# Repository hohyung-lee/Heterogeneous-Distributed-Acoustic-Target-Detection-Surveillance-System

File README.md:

# [지능형 국지 방어] 이기종 분산 처리 기반 음향 표적 탐지 및 지향성 감시 체계

**Heterogeneous Distributed Acoustic Target Detection & Surveillance System**

---

## 1. 프로젝트 목적 및 배경 (Background & Objectives)

### 방산 분야 적용

현대 전장 및 주요 보안 시설의 대드론(Anti-Drone) 체계 및 저격수 탐지 시스템에 적용되는 **'음향-시각 융합 복합 센서 체계'** 프로토타입 개발

### 이기종 분산 아키텍처 채택

단일 보드에서 모든 연산을 처리할 경우 발생하는 모터의 역기전력(Back-EMF) 및 고성능 프로세서의 스위칭 노이즈(Ground Bounce)가 초정밀 아날로그 오디오 신호에 치명적인 간섭(EMI)을 일으킴. 이를 원천 차단하기 위해 **고속 음향 처리 전용 FPGA 하드웨어**와 **영상/모터 제어용 GPU 비전 노드(Jetson)**를 물리적으로 분리하는 체계 연동 설계를 적용함.

---

## 2. 시스템 아키텍처 및 체계 연동 조감도 (System Architecture)

### Node 1 — Sensor Node (Custom FPGA Board)

```
Sound Target
  ↓ (Acoustic Wave)
4x Analog MEMS Mic
  ↓
Differential Driver (THS4551)
  ↓
ADS1274 (24-bit ADC, Simultaneous Sampling)
  ↓
Xilinx Artix-7 FPGA
  (Data Capture / Channel Sync / TDOA-DOA / UDP Packetization)
  ↓
Ethernet PHY (LAN8720A) → HR911105A (MagJack)
  ↓
UDP Transmission : "Target at θ°"
```

### 연결 인터페이스

**Standard Ethernet Cable**

### Node 2 — Command & Vision Node (Jetson Orin Nano)

```
Jetson Orin Nano
  (Direction Data Receive + Vision Processing + AI)
  ├── (PWM / GPIO) → 2-Axis Pan-Tilt Motor (Rotate to Target Direction)
  └── (MIPI / USB) → Camera Module (Target Tracking & Imaging)
```

### 보드 구성 상세

| 구분                              | 명칭                                   | 설명                                                                                                                    |
| --------------------------------- | -------------------------------------- | ----------------------------------------------------------------------------------------------------------------------- |
| **Sensor Deck**             | 마이크로폰 도터보드 (Protruding Array) | 4채널 아날로그 MEMS 마이크와 디커플링 커패시터만 실장, 3D 프린팅 하우징 외부 최상단으로 돌출 배치                       |
| **Processing & Power Core** | 메인보드 (Enclosed Base)               | Artix-7 FPGA, 차동 드라이버(FDA), ADC, 전원부, Ethernet PHY, MagJack 등 노이즈/발열 발생원을 3D 하우징 내부에 밀폐 실장 |
| **Interface**               | Board-to-Board 연결                    | 저레벨 아날로그 마이크 출력 및 전원 라인의 무결성 유지를 위해 쉴딩 처리된 FPC 케이블 체결                               |

---

## 3. 하드웨어 주요 사양 (Hardware Specifications — Sensor Node)

| 항목                        | 사양                                                                                                   |
| --------------------------- | ------------------------------------------------------------------------------------------------------ |
| **Main Processor**    | AMD Xilinx Artix-7 (XC7A35T-1CSG325C) — Bare-metal Chip-down                                          |
| **Sensor Array**      | Infineon IM68A130A Analog MEMS Microphone × 4ea                                                       |
| **Analog Front-End**  | TI THS4551 (Fully Differential Amplifier)                                                              |
| **Data Converter**    | TI ADS1274 (24-bit Simultaneous Sampling ADC)                                                          |
| **Network Interface** | Microchip LAN8720A (10/100M Ethernet PHY, RMII) + HanRun HR911105A (MagJack) + 50MHz Active Oscillator |
| **Configuration**     | Winbond W25Q32 (32Mbit SPI Flash) / JTAG Interface                                                     |
| **PCB 스펙**          | 4-Layer FR-4 (L1: Signal/USER – L2: Solid GND – L3: VCC/Power – L4: Signal/USER), 두께 1.6mm        |
| **EDA Tool**          | KiCad (회로도, PCB Artwork, 3D Rendering, Impedance Calculation)                                       |

### Power Tree

| 레일 | 용도          | 소자                          |
| ---- | ------------- | ----------------------------- |
| 1.0V | FPGA Core     | TI TLV62569 Buck Converter    |
| 3.3V | FPGA I/O      | TI TLV62569 Buck Converter    |
| 3.3V | MEMS Mic      | TI LP5907 Ultra-Low Noise LDO |
| 1.8V | ADC DVDD      | TI LP5907 1.8V LDO            |
| 2.5V | ADC Reference | TI REF5025                    |

### Form Factor

| 보드          | 크기                                               |
| ------------- | -------------------------------------------------- |
| Mainboard     | 100mm × 100mm (DFM 및 양산 단가 최적화 규격)      |
| Daughterboard | 50mm × 50mm 이내 십자형 구조 (마이크 어레이 전용) |

---

## 4. 하드웨어 설계 핵심 기술 (Core Hardware Design Technologies)

### ① 물리적 노이즈 격리 및 전원 무결성 (Power Integrity)

- **시스템 분리** — 모터 구동부와 고성능 GPU(Jetson)를 물리적으로 분리하여 아날로그 센서부의 GND 흔들림 및 전원 강하 현상 방지
- **초저노이즈 전원 트리(Power Tree)**
  - FPGA Core(1.0V) 및 I/O(3.3V) : 스위칭 강하 효율을 위한 고성능 Buck Converter 적용
  - MEMS Mic(3.3V), ADC Analog Rail, ADC DVDD(1.8V) : 디지털 스위칭 노이즈 차단을 위해 별도의 초저노이즈 LDO 및 기준 전압 레퍼런스 적용
  - Ethernet PHY 아날로그 전원은 Ferrite Bead 후단의 ETH_3V3_A로 분리 공급

### ② 고속 신호 무결성 (Signal Integrity) 및 4-Layer 임피던스 제어

- **4-Layer Stackup 최적화** — `L1(Top Signal) - L2(Solid GND) - L3(Power/VCC) - L4(Bottom Signal)`의 정석적인 4층 구조 채택. 2층(L2)에 끊어짐 없는 완벽한 GND 플레인을 깔아 기판 내 모든 고속 신호의 최단 리턴 패스(Return Path)를 보장하고 고주파 방사 노이즈(EMI)를 원천 차단함.
- **차동 배선(Differential Pair)** — Ethernet PHY ↔ MagJack 간 TX/RX 라인에 대한 100Ω 차동 임피던스 매칭을 수행하며, L2 GND 레퍼런스 플레인을 기준으로 KiCad 임피던스 계산기를 통해 산출된 배선폭/간격을 Artwork에 적용함.
- **Mixed-Signal 프런트엔드** — 4채널 아날로그 마이크 출력을 FDA로 차동 변환한 뒤 ADS1274에 입력하여 공통모드 노이즈 내성 확보
- **동시 샘플링(Simultaneous Sampling)** — ADS1274의 4채널 동시 샘플링을 이용하여 TDOA 연산에 필요한 채널 간 시간 정합성 확보
- **클록 무결성(Clock Integrity)** — ADC 전용 저지터 클록과 Ethernet용 50MHz REF_CLK를 분리하여 각 인터페이스의 지터 민감도를 관리

### ③ Chip-down 기반 FPGA 인프라 자력 설계

- 기성품 평가 보드(Eval Board) 배제, FPGA 구동을 위한 최소 시스템(Minimum System) 직접 설계
- 데이터시트 분석을 통한 Power-On Reset(POR), Configuration Flash, JTAG 디버그 회로 독자 구현
- FPGA 내부 로직 : ADS1274 디지털 데이터 수집 → 채널 정렬/버퍼링 → TDOA/DOA 연산 → Ethernet UDP 패킷화

### ④ 기구-전자 통합 설계 및 음향학적 최적화 (Acoustic-Mechanical Integration)

- **음향 그림자(Acoustic Shadowing) 및 공명 차단** — 단일 보드 설계 시 대형/고발열 소자에 의한 소리 회절과 케이스 내부 빈 공간의 헬름홀츠 공명(Helmholtz Resonance) 왜곡 방지. 마이크 어레이 보드를 케이스 외부로 돌출 분리시켜 360° 완벽한 음향 시야(Line-of-Sight) 확보
- **센서 지오메트리 설계** — 공간 앨리어싱(Spatial Aliasing, ≤21.25mm @ 8kHz) 한계와 샘플링 시간 분해능을 고려하여 TDOA 알고리즘 최적의 30~40mm 정사각형 마이크 배치 간격 도출

---

## 5. 기대 효과 및 포트폴리오 소구점 (Expected Impact)

이 프로젝트는 단위 칩 수준의 정밀한 하드웨어 설계 능력(SI/PI, 4-Layer Artwork)을 갖추었을 뿐만 아니라, 전체 무기 체계의 데이터 흐름과 노이즈 간섭(EMC)을 이해하고 최적의 아키텍처를 설계하는 **시스템 엔지니어링 역량**을 겸비했음을 증명함.

특히 방위산업에서 가장 민감하게 다루는 아날로그 센서 신호의 신뢰성, Mixed-Signal 프런트엔드 설계, FPGA 기반 실시간 TDOA/DOA 연산, 체계 연동 통신(Ethernet, UDP)을 실제 구현함으로써, 입사 후 즉각적으로 실무 하드웨어 R&D 프로젝트에 투입될 수 있는 준비된 인재임을 어필함.

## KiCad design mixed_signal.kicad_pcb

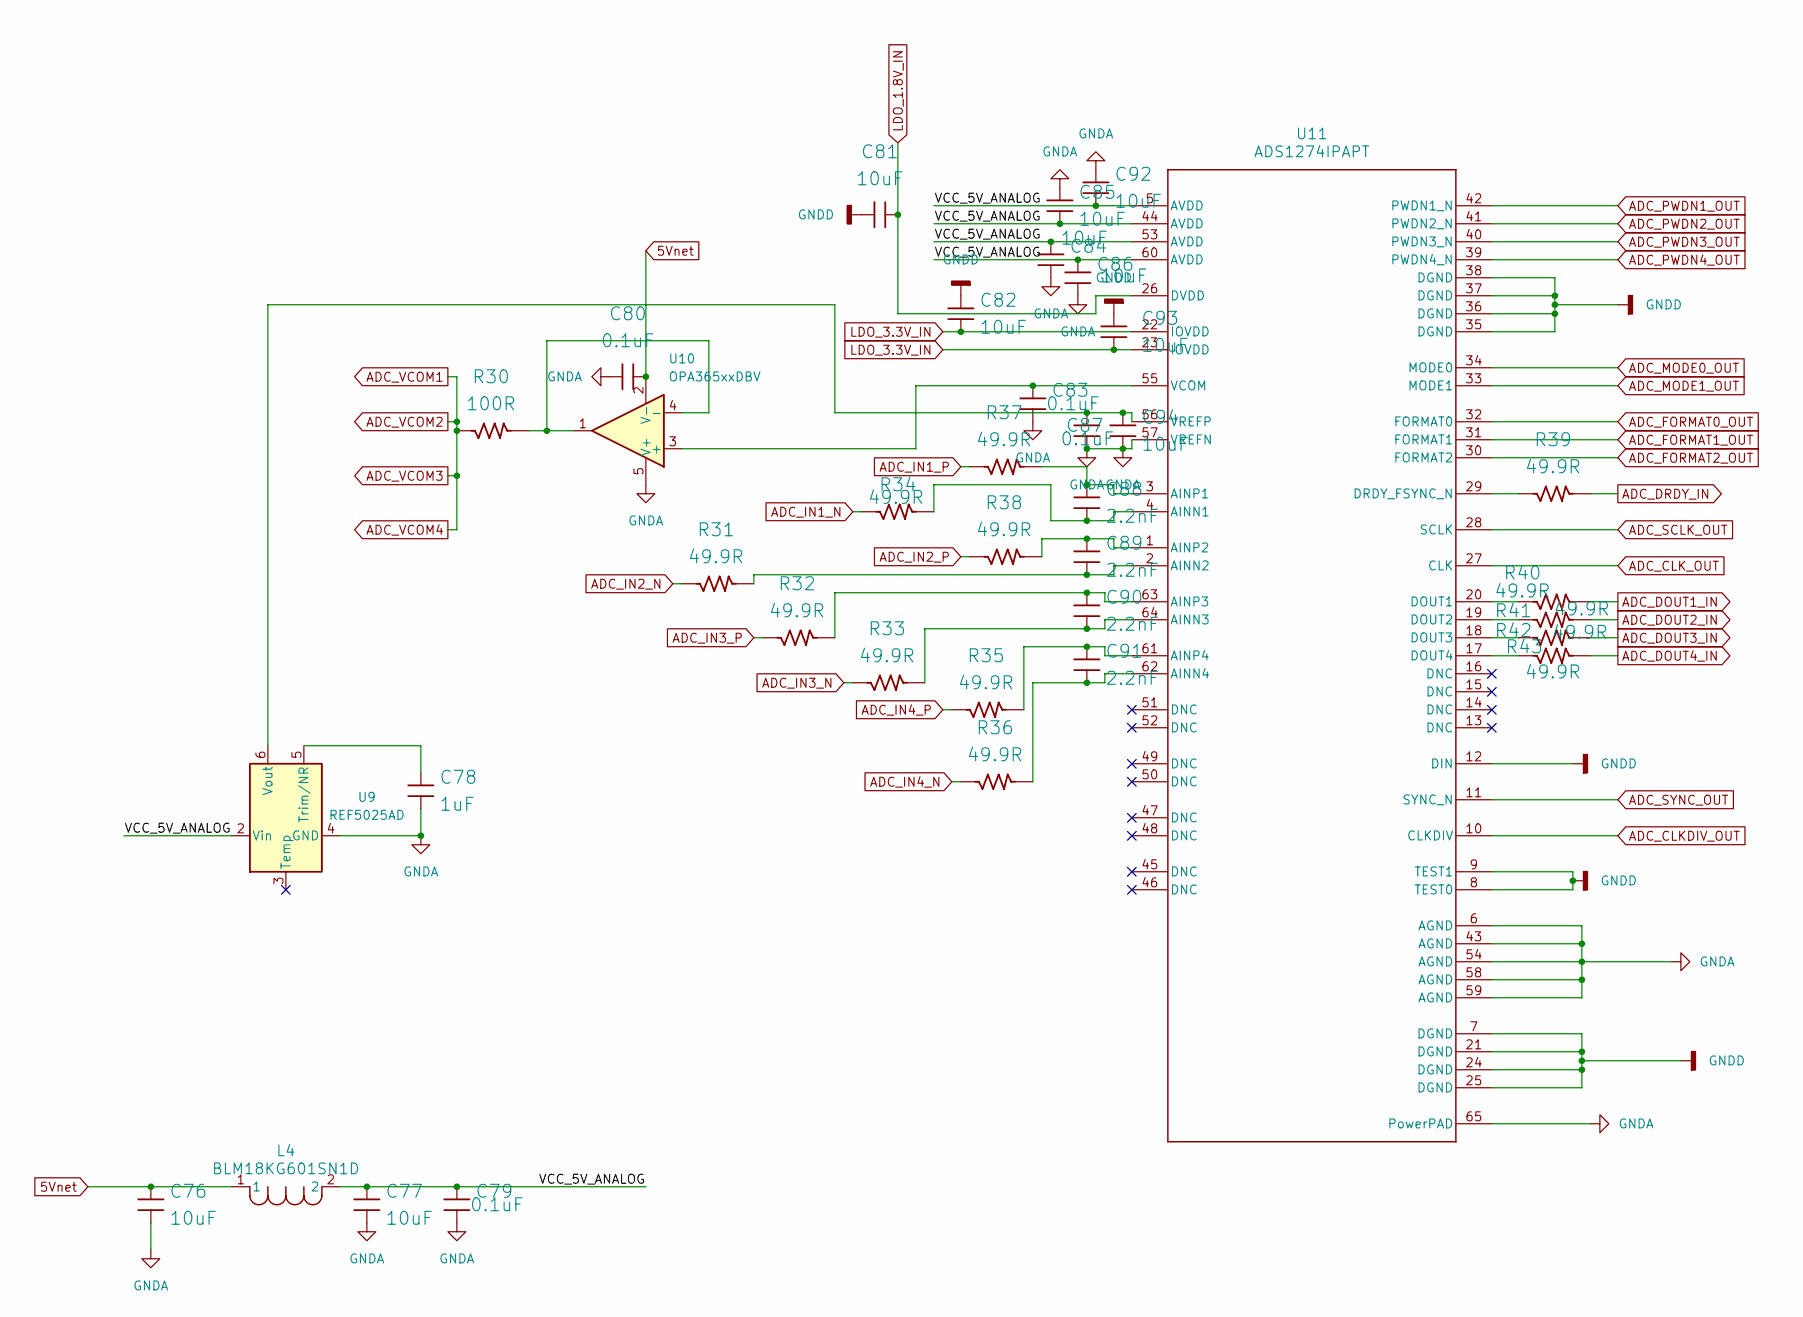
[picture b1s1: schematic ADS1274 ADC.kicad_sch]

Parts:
C76, C77, C81, C82, C84, C85, C86, C92, C93, C94: 10uF; CAP_1206; Manufacturer Part Number CL31B106KBHNNNE
C78: 1uF; CAP_0805; Manufacturer Part Number CC0805JKX7R9BB105
C79, C80, C83, C87: 0.1uF; CAP_0805; Manufacturer Part Number 08055C104JAT4A
C88, C89, C90, C91: 2.2nF; CAP_0805; Manufacturer Part Number C0805C222K5GEC7800
L4: BLM18KG601SN1D; IND_BLM18KG601SN1D_MUR
R30: 100R; RES_0805; Manufacturer Part Number WR08X1000FTL
R31, R32, R33, R34, R35, R36, R37, R38, R39, R40, R41, R42, R43: 49.9R; RES_0805; Manufacturer Part Number WR12X49R9FTL
U9: REF5025AD; SOIC-8_3.9x4.9mm_P1.27mm
U10: OPA365xxDBV; SOT-23-5
U11: ADS1274IPAPT; PAP0064G-IPC_A

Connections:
5Vnet: C76.2, C80.2, L4.1, U10.2 (V-); also elsewhere on the board
/ADS1274 ADC/VCC_5V_ANALOG: C77.2, C79.2, C84.2, C85.1, C86.2, C92.1, L4.2, U9.2 (Vin), U11.5 (AVDD), U11.44 (AVDD), U11.53 (AVDD), U11.60 (AVDD)
ADC_CLKDIV_OUT: U11.10 (CLKDIV); also elsewhere on the board
ADC_CLK_OUT: U11.27 (CLK); also elsewhere on the board
ADC_DOUT1_IN: R40.2; also elsewhere on the board
ADC_DOUT2_IN: R41.2; also elsewhere on the board
ADC_DOUT3_IN: R42.2; also elsewhere on the board
ADC_DOUT4_IN: R43.2; also elsewhere on the board
ADC_DRDY_IN: R39.2; also elsewhere on the board
ADC_FORMAT0_OUT: U11.32 (FORMAT0); also elsewhere on the board
ADC_FORMAT1_OUT: U11.31 (FORMAT1); also elsewhere on the board
ADC_FORMAT2_OUT: U11.30 (FORMAT2); also elsewhere on the board
ADC_IN1_N: R34.1; also elsewhere on the board
ADC_IN1_P: R37.1; also elsewhere on the board
ADC_IN2_N: R31.1; also elsewhere on the board
ADC_IN2_P: R38.1; also elsewhere on the board
ADC_IN3_N: R33.1; also elsewhere on the board
ADC_IN3_P: R32.1; also elsewhere on the board
ADC_IN4_N: R36.1; also elsewhere on the board
ADC_IN4_P: R35.1; also elsewhere on the board
ADC_MODE0_OUT: U11.34 (MODE0); also elsewhere on the board
ADC_MODE1_OUT: U11.33 (MODE1); also elsewhere on the board
ADC_PWDN1_OUT: U11.42 (PWDN1_N); also elsewhere on the board
ADC_PWDN2_OUT: U11.41 (PWDN2_N); also elsewhere on the board
ADC_PWDN3_OUT: U11.40 (PWDN3_N); also elsewhere on the board
ADC_PWDN4_OUT: U11.39 (PWDN4_N); also elsewhere on the board
ADC_SCLK_OUT: U11.28 (SCLK); also elsewhere on the board
ADC_SYNC_OUT: U11.11 (SYNC_N); also elsewhere on the board
ADC_VCOM1: R30.1; also elsewhere on the board
GNDA: C76.1, C77.1, C78.1, C79.1, C80.1, C83.1, C84.1, C85.2, C86.1, C87.1, C92.2, C94.1, U9.4 (GND), U10.5 (V+), U11.6 (AGND), U11.43 (AGND), U11.54 (AGND), U11.57 (VREFN), U11.58 (AGND), U11.59 (AGND), U11.65 (PowerPAD); also elsewhere on the board
GNDD: C81.1, C82.2, C93.2, U11.7 (DGND), U11.8 (TEST0), U11.9 (TEST1), U11.12 (DIN), U11.21 (DGND), U11.24 (DGND), U11.25 (DGND), U11.35 (DGND), U11.36 (DGND), U11.37 (DGND), U11.38 (DGND)
LDO_1.8V_IN: C81.2, U11.26 (DVDD); also elsewhere on the board
LDO_3.3V_IN: C82.1, C93.1, U11.22 (IOVDD), U11.23 (IOVDD); also elsewhere on the board
unnamed: C78.2, U9.5 (Trim/NR)
unnamed: C83.2, U10.3 (+), U11.55 (VCOM)
unnamed: R30.2, U10.1, U10.4 (-)
unnamed: C88.1, R34.2, U11.4 (AINN1)
unnamed: C89.1, R31.2, U11.2 (AINN2)
unnamed: C90.1, R33.2, U11.64 (AINN3)
unnamed: C91.1, R36.2, U11.62 (AINN4)
unnamed: C88.2, R37.2, U11.3 (AINP1)
unnamed: C89.2, R38.2, U11.1 (AINP2)
unnamed: C90.2, R32.2, U11.63 (AINP3)
unnamed: C91.2, R35.2, U11.61 (AINP4)
unnamed: R40.1, U11.20 (DOUT1)
unnamed: R41.1, U11.19 (DOUT2)
unnamed: R42.1, U11.18 (DOUT3)
unnamed: R43.1, U11.17 (DOUT4)
unnamed: R39.1, U11.29 (DRDY_FSYNC_N)
unnamed: C87.2, C94.2, U9.6 (Vout), U11.56 (VREFP)

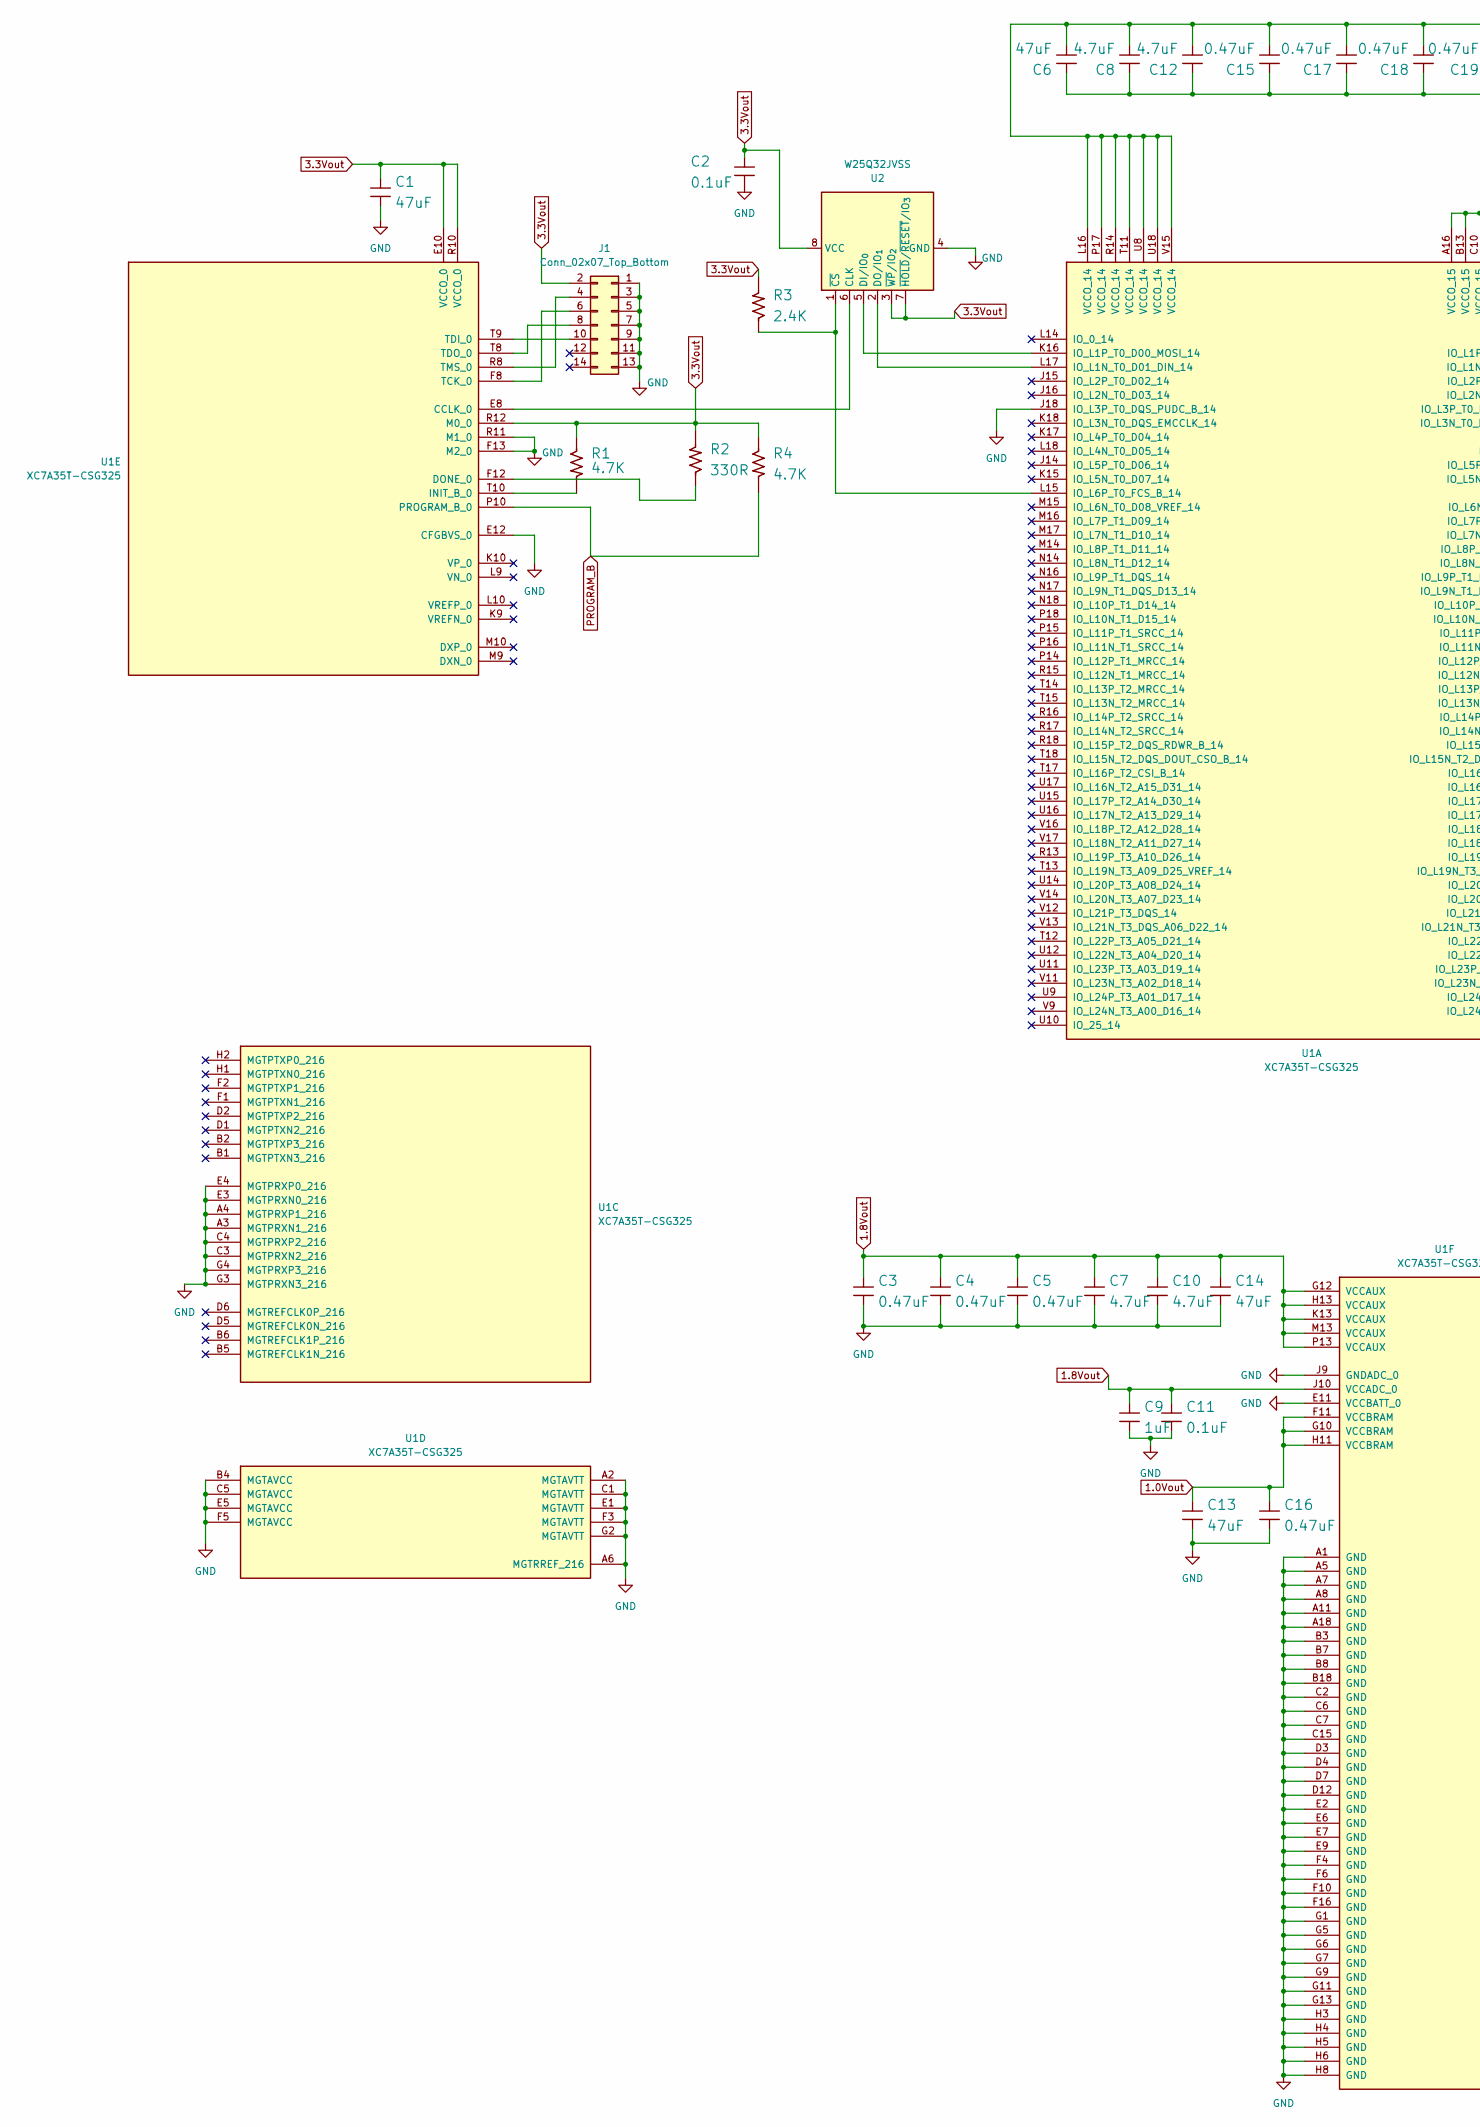
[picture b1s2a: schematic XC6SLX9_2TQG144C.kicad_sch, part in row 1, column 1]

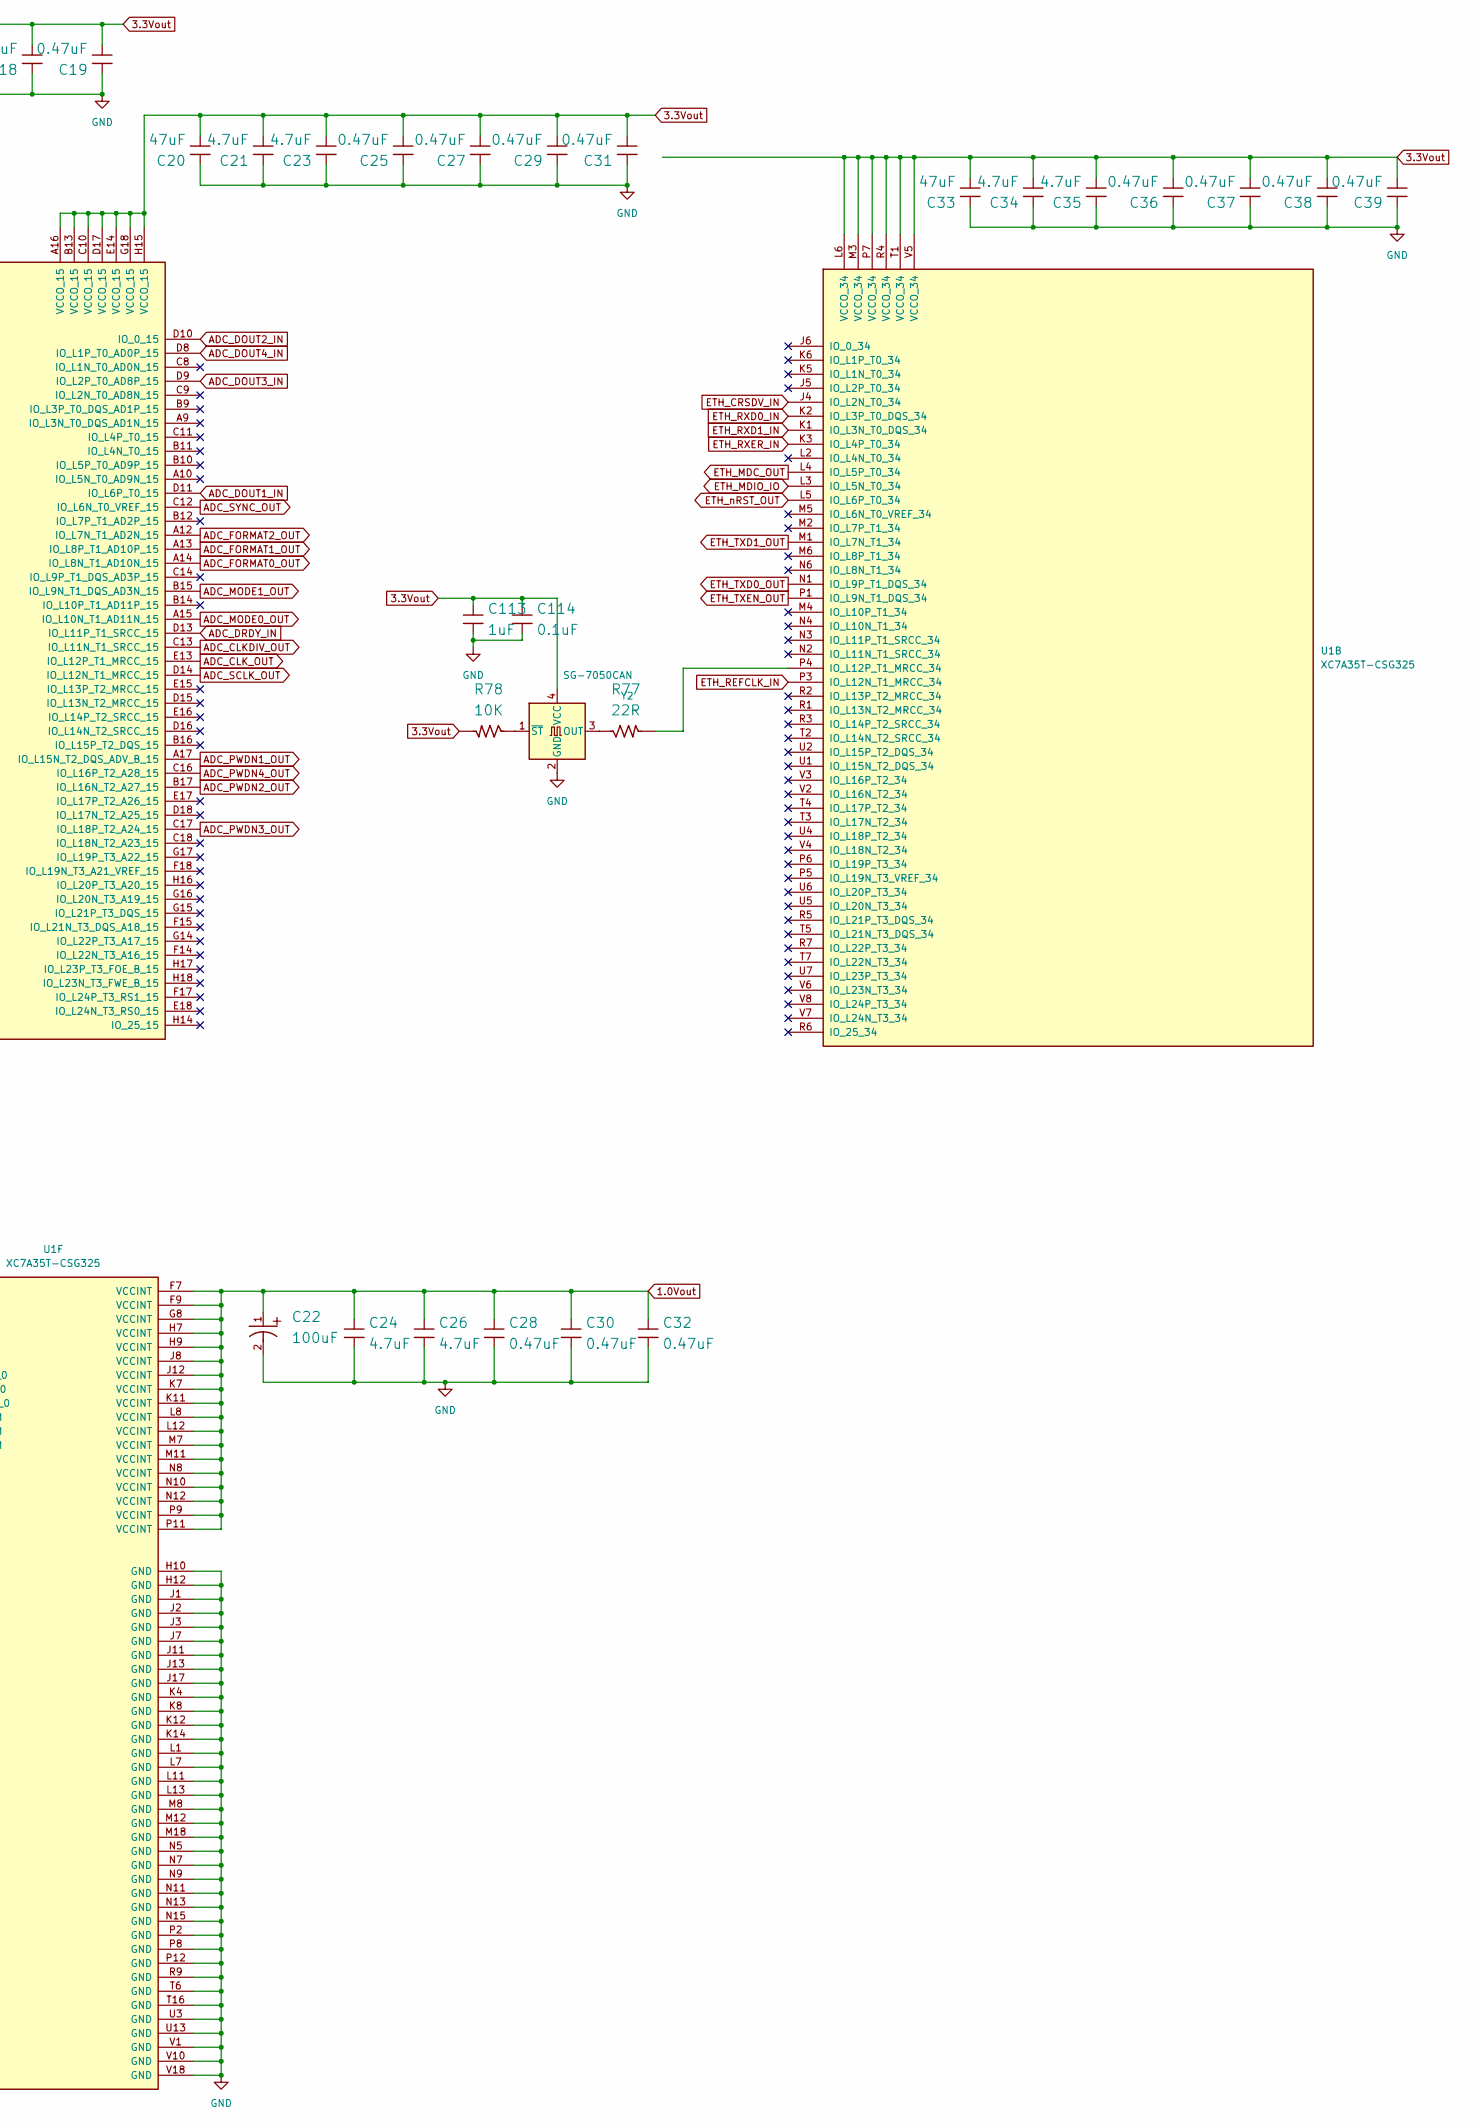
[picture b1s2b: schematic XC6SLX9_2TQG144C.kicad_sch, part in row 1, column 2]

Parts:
C1, C6, C13, C14, C20, C33: 47uF; CAP_0805; Manufacturer Part Number GRM21BR61H475KE51L
C2, C11: 0.1uF; CAP_0805; Manufacturer Part Number 08055C104JAT4A
C3, C4, C5, C15, C16, C17, C18, C19, C25, C27, C28, C29, C30, C31, C32, C36, C37, C38, C39: 0.47uF; CAP_0805; Manufacturer Part Number C0805C474J5RACTU
C7, C8, C10, C12, C21, C23, C24, C26, C34, C35: 4.7uF; CAP_0805; Manufacturer Part Number GRM21BR61H475KE51L
C9, C113: 1uF; CAP_0805; Manufacturer Part Number CC0805JKX7R9BB105
C22: 100uF; ACAP_P236_D305_H303_RAD; Manufacturer Part Number UWT1E101MCL1GS
C114: 0.1uF; CAP_0805; Manufacturer Part Number CL21B104KBCNNNC
J1: Conn_02x07_Top_Bottom; PinHeader_2x07_P2.54mm_Vertical
R1, R4: 4.7K; RES_0805; Manufacturer Part Number RC0805FR-074K7L
R2: 330R; RES_0805; Manufacturer Part Number WR08X3300FTL
R3: 2.4K; RES_0805; Manufacturer Part Number RC0805FR-072KL
R77: 22R; RES_0805; Manufacturer Part Number WR08X2200FTL
R78: 10K; RES_0805; Manufacturer Part Number WR08X1002FTL
U1: XC7A35T-CSG325; Xilinx_CSG325
U2: W25Q32JVSS; SOIC-8_5.3x5.3mm_P1.27mm
Y2: SG-7050CAN; Oscillator_SMD_SeikoEpson_SG8002CA-4Pin_7.0x5.0mm

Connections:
1.0Vout: C13.2, C16.2, C22.1, C24.2, C26.2, C28.2, C30.2, C32.2, U1.F7 (VCCINT), U1.F9 (VCCINT), U1.F11 (VCCBRAM), U1.G8 (VCCINT), U1.G10 (VCCBRAM), U1.H7 (VCCINT), U1.H9 (VCCINT), U1.H11 (VCCBRAM), U1.J8 (VCCINT), U1.J12 (VCCINT), U1.K7 (VCCINT), U1.K11 (VCCINT), U1.L8 (VCCINT), U1.L12 (VCCINT), U1.M7 (VCCINT), U1.M11 (VCCINT), U1.N8 (VCCINT), U1.N10 (VCCINT), U1.N12 (VCCINT), U1.P9 (VCCINT), U1.P11 (VCCINT); also elsewhere on the board
1.8Vout: C3.2, C4.2, C5.2, C7.2, C9.2, C10.2, C11.2, C14.2, U1.G12 (VCCAUX), U1.H13 (VCCAUX), U1.J10 (VCCADC_0), U1.K13 (VCCAUX), U1.M13 (VCCAUX), U1.P13 (VCCAUX); also elsewhere on the board
3.3Vout: C1.2, C2.2, C6.1, C8.1, C12.1, C15.1, C17.1, C18.1, C19.1, C20.1, C21.1, C23.1, C25.1, C27.1, C29.1, C31.1, C33.1, C34.1, C35.1, C36.1, C37.1, C38.1, C39.1, C113.2, C114.2, J1.2 (Pin_8), R1.1, R2.2, R3.2, R4.1, R78.2, U1.A16 (VCCO_15), U1.B13 (VCCO_15), U1.C10 (VCCO_15), U1.D17 (VCCO_15), U1.E10 (VCCO_0), U1.E14 (VCCO_15), U1.G18 (VCCO_15), U1.H15 (VCCO_15), U1.L6 (VCCO_34), U1.L16 (VCCO_14), U1.M3 (VCCO_34), U1.P7 (VCCO_34), U1.P17 (VCCO_14), U1.R4 (VCCO_34), U1.R10 (VCCO_0), U1.R12 (M0_0), U1.R14 (VCCO_14), U1.T1 (VCCO_34), U1.T11 (VCCO_14), U1.U8 (VCCO_14), U1.U18 (VCCO_14), U1.V5 (VCCO_34), U1.V15 (VCCO_14), U2.3 (~WP/IO_{2}), U2.7 (~HOLD/~RESET/IO_{3}), U2.8 (VCC), Y2.4 (VCC); also elsewhere on the board
+3V3: C1.1, C2.1, C3.1, C4.1, C5.1, C6.2, C7.1, C8.2, C9.1, C10.1, C11.1, C12.2, C13.1, C14.1, C15.2, C16.1, C17.2, C18.2, C19.2, C20.2, C21.2, C22.2, C23.2, C24.1, C25.2, C26.1, C27.2, C28.1, C29.2, C30.1, C31.2, C32.1, C33.2, C34.2, C35.2, C36.2, C37.2, C38.2, C39.2, C113.1, C114.1, J1.1, J1.3 (Pin_2), J1.5 (Pin_3), J1.7 (Pin_4), J1.9 (Pin_5), J1.11 (Pin_6), J1.13 (Pin_7), U1.A1 (GND), U1.A2 (MGTAVTT), U1.A3 (MGTPRXN1_216), U1.A4 (MGTPRXP1_216), U1.A5 (GND), U1.A6 (MGTRREF_216), U1.A7 (GND), U1.A8 (GND), U1.A11 (GND), U1.A18 (GND), U1.B3 (GND), U1.B4 (MGTAVCC), U1.B7 (GND), U1.B8 (GND), U1.B18 (GND), U1.C1 (MGTAVTT), U1.C2 (GND), U1.C3 (MGTPRXN2_216), U1.C4 (MGTPRXP2_216), U1.C5 (MGTAVCC), U1.C6 (GND), U1.C7 (GND), U1.C15 (GND), U1.D3 (GND), U1.D4 (GND), U1.D7 (GND), U1.D12 (GND), U1.E1 (MGTAVTT), U1.E2 (GND), U1.E3 (MGTPRXN0_216), U1.E4 (MGTPRXP0_216), U1.E5 (MGTAVCC), U1.E6 (GND), U1.E7 (GND), U1.E9 (GND), U1.E11 (VCCBATT_0), U1.E12 (CFGBVS_0), U1.F3 (MGTAVTT), U1.F4 (GND), U1.F5 (MGTAVCC), U1.F6 (GND), U1.F10 (GND), U1.F13 (M2_0), U1.F16 (GND), U1.G1 (GND), U1.G2 (MGTAVTT), U1.G3 (MGTPRXN3_216), U1.G4 (MGTPRXP3_216), U1.G5 (GND), U1.G6 (GND), U1.G7 (GND), U1.G9 (GND), U1.G11 (GND), U1.G13 (GND), U1.H3 (GND), U1.H4 (GND), U1.H5 (GND), U1.H6 (GND), U1.H8 (GND), U1.H10 (GND), U1.H12 (GND), U1.J1 (GND), U1.J2 (GND), U1.J3 (GND), U1.J7 (GND), U1.J9 (GNDADC_0), U1.J11 (GND), U1.J13 (GND), U1.J17 (GND), U1.J18 (IO_L3P_T0_DQS_PUDC_B_14), U1.K4 (GND), U1.K8 (GND), U1.K12 (GND), U1.K14 (GND), U1.L1 (GND), U1.L7 (GND), U1.L11 (GND), U1.L13 (GND), U1.M8 (GND), U1.M12 (GND), U1.M18 (GND), U1.N5 (GND), U1.N7 (GND), U1.N9 (GND), U1.N11 (GND), U1.N13 (GND), U1.N15 (GND), U1.P2 (GND), U1.P8 (GND), U1.P12 (GND), U1.R9 (GND), U1.R11 (M1_0), U1.T6 (GND), U1.T16 (GND), U1.U3 (GND), U1.U13 (GND), U1.V1 (GND), U1.V10 (GND), U1.V18 (GND), U2.4 (GND), Y2.2 (GND); also elsewhere on the board
ADC_CLKDIV_OUT: U1.C13 (IO_L11N_T1_SRCC_15); also elsewhere on the board
ADC_CLK_OUT: U1.E13 (IO_L12P_T1_MRCC_15); also elsewhere on the board
ADC_DOUT1_IN: U1.D11 (IO_L6P_T0_15); also elsewhere on the board
ADC_DOUT2_IN: U1.D10 (IO_0_15); also elsewhere on the board
ADC_DOUT3_IN: U1.D9 (IO_L2P_T0_AD8P_15); also elsewhere on the board
ADC_DOUT4_IN: U1.D8 (IO_L1P_T0_AD0P_15); also elsewhere on the board
ADC_DRDY_IN: U1.D13 (IO_L11P_T1_SRCC_15); also elsewhere on the board
ADC_FORMAT0_OUT: U1.A14 (IO_L8N_T1_AD10N_15); also elsewhere on the board
ADC_FORMAT1_OUT: U1.A13 (IO_L8P_T1_AD10P_15); also elsewhere on the board
ADC_FORMAT2_OUT: U1.A12 (IO_L7N_T1_AD2N_15); also elsewhere on the board
ADC_MODE0_OUT: U1.A15 (IO_L10N_T1_AD11N_15); also elsewhere on the board
ADC_MODE1_OUT: U1.B15 (IO_L9N_T1_DQS_AD3N_15); also elsewhere on the board
ADC_PWDN1_OUT: U1.A17 (IO_L15N_T2_DQS_ADV_B_15); also elsewhere on the board
ADC_PWDN2_OUT: U1.B17 (IO_L16N_T2_A27_15); also elsewhere on the board
ADC_PWDN3_OUT: U1.C17 (IO_L18P_T2_A24_15); also elsewhere on the board
ADC_PWDN4_OUT: U1.C16 (IO_L16P_T2_A28_15); also elsewhere on the board
ADC_SCLK_OUT: U1.D14 (IO_L12N_T1_MRCC_15); also elsewhere on the board
ADC_SYNC_OUT: U1.C12 (IO_L6N_T0_VREF_15); also elsewhere on the board
ETH_CRSDV_IN: U1.J4 (IO_L2N_T0_34); also elsewhere on the board
ETH_MDC_OUT: U1.L4 (IO_L5P_T0_34); also elsewhere on the board
ETH_MDIO_IO: U1.L3 (IO_L5N_T0_34); also elsewhere on the board
ETH_REFCLK_IN: U1.P3 (IO_L12N_T1_MRCC_34); also elsewhere on the board
ETH_RXD0_IN: U1.K2 (IO_L3P_T0_DQS_34); also elsewhere on the board
ETH_RXD1_IN: U1.K1 (IO_L3N_T0_DQS_34); also elsewhere on the board
ETH_RXER_IN: U1.K3 (IO_L4P_T0_34); also elsewhere on the board
ETH_TXD0_OUT: U1.N1 (IO_L9P_T1_DQS_34); also elsewhere on the board
ETH_TXD1_OUT: U1.M1 (IO_L7N_T1_34); also elsewhere on the board
ETH_TXEN_OUT: U1.P1 (IO_L9N_T1_DQS_34); also elsewhere on the board
ETH_nRST_OUT: U1.L5 (IO_L6P_T0_34); also elsewhere on the board
unnamed: J1.4 (Pin_9), U1.R8 (TMS_0)
unnamed: J1.6 (Pin_10), U1.F8 (TCK_0)
unnamed: J1.8 (Pin_11), U1.T8 (TDO_0)
unnamed: J1.10 (Pin_12), U1.T9 (TDI_0)
unnamed: R77.1, Y2.3 (OUT)
unnamed: R77.2, U1.P4 (IO_L12P_T1_MRCC_34)
unnamed: R78.1, Y2.1 (~ST)
unnamed: U1.L17 (IO_L1N_T0_D01_DIN_14), U2.2 (DO/IO_{1})
unnamed: U1.K16 (IO_L1P_T0_D00_MOSI_14), U2.5 (DI/IO_{0})
unnamed: R3.1, U1.L15 (IO_L6P_T0_FCS_B_14), U2.1 (~CS)
unnamed: U1.E8 (CCLK_0), U2.6 (CLK)
unnamed: R2.1, U1.F12 (DONE_0)
unnamed: R1.2, U1.T10 (INIT_B_0)
PROGRAM_B: R4.2, U1.P10 (PROGRAM_B_0)

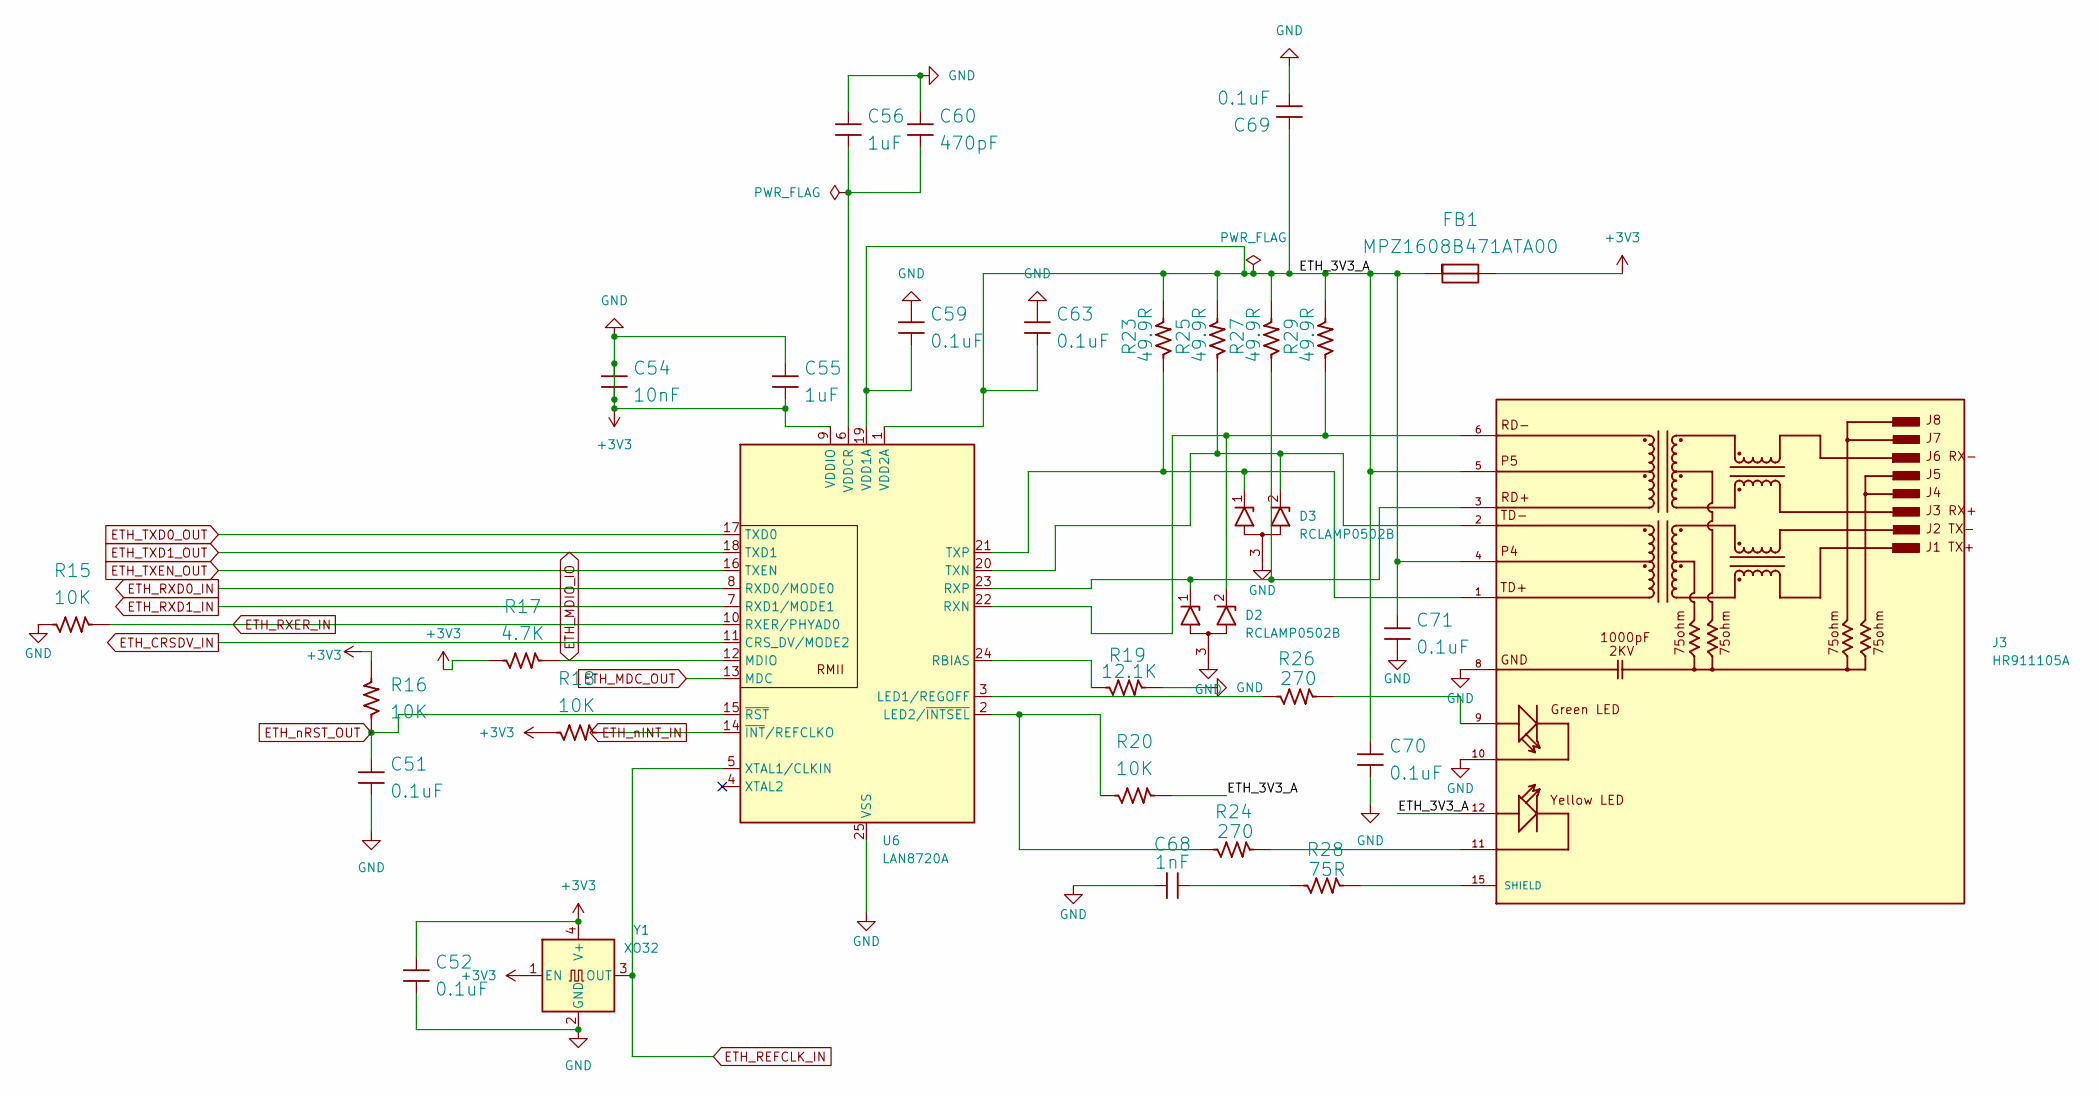
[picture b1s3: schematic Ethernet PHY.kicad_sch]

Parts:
C51, C52, C59, C63, C69, C70, C71: 0.1uF; CAP_0805; Manufacturer Part Number CL21B104KBCNNNC
C54: 10nF; CAP_0805; Manufacturer Part Number C0805C103K5RECAUTO
C55, C56: 1uF; CAP_0805; Manufacturer Part Number CC0805JKX7R9BB105
C60: 470pF; CAP_0805; Manufacturer Part Number C0805C471J5GACTU
C68: 1nF; CAP_0805; Manufacturer Part Number C0805C102K2GECAUTO
D2, D3: RCLAMP0502B; SOT-416
FB1: MPZ1608B471ATA00; L_0603_1608Metric; Manufacturer Part Number MPZ1608B471ATA00
J3: HR911105A; HANRUN_HR911105A; PARTREV A
R15, R16, R18, R20: 10K; RES_0603; Manufacturer Part Number WR06X1002FTL
R17: 4.7K; RES_0603; Manufacturer Part Number WR06X4701FTL
R19: 12.1K; RES_0603; Manufacturer Part Number WR06X1002FTL
R23, R25, R27, R29: 49.9R; RES_0805; Manufacturer Part Number WR12X49R9FTL
R24, R26: 270; RES_0603; Manufacturer Part Number NA
R28: 75R; RES_0603; Manufacturer Part Number CR0603-FX-7500ELF
U6: LAN8720A; VQFN-24-1EP_4x4mm_P0.5mm_EP2.5x2.5mm_ThermalVias
Y1: XO32; Oscillator_SMD_EuroQuartz_XO32-4Pin_3.2x2.5mm

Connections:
+3V3: C51.1, C52.1, C52.2, C54.1, C54.2, C55.1, C55.2, C56.2, C59.2, C60.2, C63.2, C68.1, C69.1, C70.1, C71.1, D2.3 (A), D3.3 (A), FB1.2, J3.8, J3.10, R15.1, R16.2, R17.1, R18.1, R19.2, U6.9 (VDDIO), U6.25 (VSS), Y1.1 (EN), Y1.2 (GND), Y1.4 (V+); also elsewhere on the board
/Ethernet PHY/ETH_3V3_A: C59.1, C63.1, C69.2, C70.2, C71.2, FB1.1, J3.4, J3.5, J3.12, R20.2, R23.2, R25.2, R27.2, R29.2, U6.1 (VDD2A), U6.19 (VDD1A)
ETH_CRSDV_IN: U6.11 (CRS_DV/MODE2); also elsewhere on the board
ETH_MDC_OUT: U6.13 (MDC); also elsewhere on the board
ETH_MDIO_IO: R17.2, U6.12 (MDIO); also elsewhere on the board
ETH_REFCLK_IN: U6.5 (XTAL1/CLKIN), Y1.3 (OUT); also elsewhere on the board
ETH_RXD0_IN: U6.8 (RXD0/MODE0); also elsewhere on the board
ETH_RXD1_IN: U6.7 (RXD1/MODE1); also elsewhere on the board
ETH_RXER_IN: R15.2, U6.10 (RXER/PHYAD0); also elsewhere on the board
ETH_TXD0_OUT: U6.17 (TXD0); also elsewhere on the board
ETH_TXD1_OUT: U6.18 (TXD1); also elsewhere on the board
ETH_TXEN_OUT: U6.16 (TXEN); also elsewhere on the board
ETH_nINT_IN: R18.2, U6.14 (~INT/REFCLKO)
ETH_nRST_OUT: C51.2, R16.1, U6.15 (~RST); also elsewhere on the board
unnamed: C68.2, R28.1
unnamed: D2.1 (K1), J3.3, R27.1, U6.23 (RXP)
unnamed: D2.2 (K2), J3.6, R29.1, U6.22 (RXN)
unnamed: D3.1 (K1), J3.1, R23.1, U6.21 (TXP)
unnamed: D3.2 (K2), J3.2, R25.1, U6.20 (TXN)
unnamed: J3.9, R26.2
unnamed: J3.11, R24.2
unnamed: J3.15 (SHIELD), J3.16 (SHIELD), R28.2
unnamed: R26.1, U6.3 (LED1/REGOFF)
unnamed: R20.1, R24.1, U6.2 (LED2/~INTSEL)
unnamed: R19.1, U6.24 (RBIAS)
unnamed: C56.1, C60.1, U6.6 (VDDCR)
